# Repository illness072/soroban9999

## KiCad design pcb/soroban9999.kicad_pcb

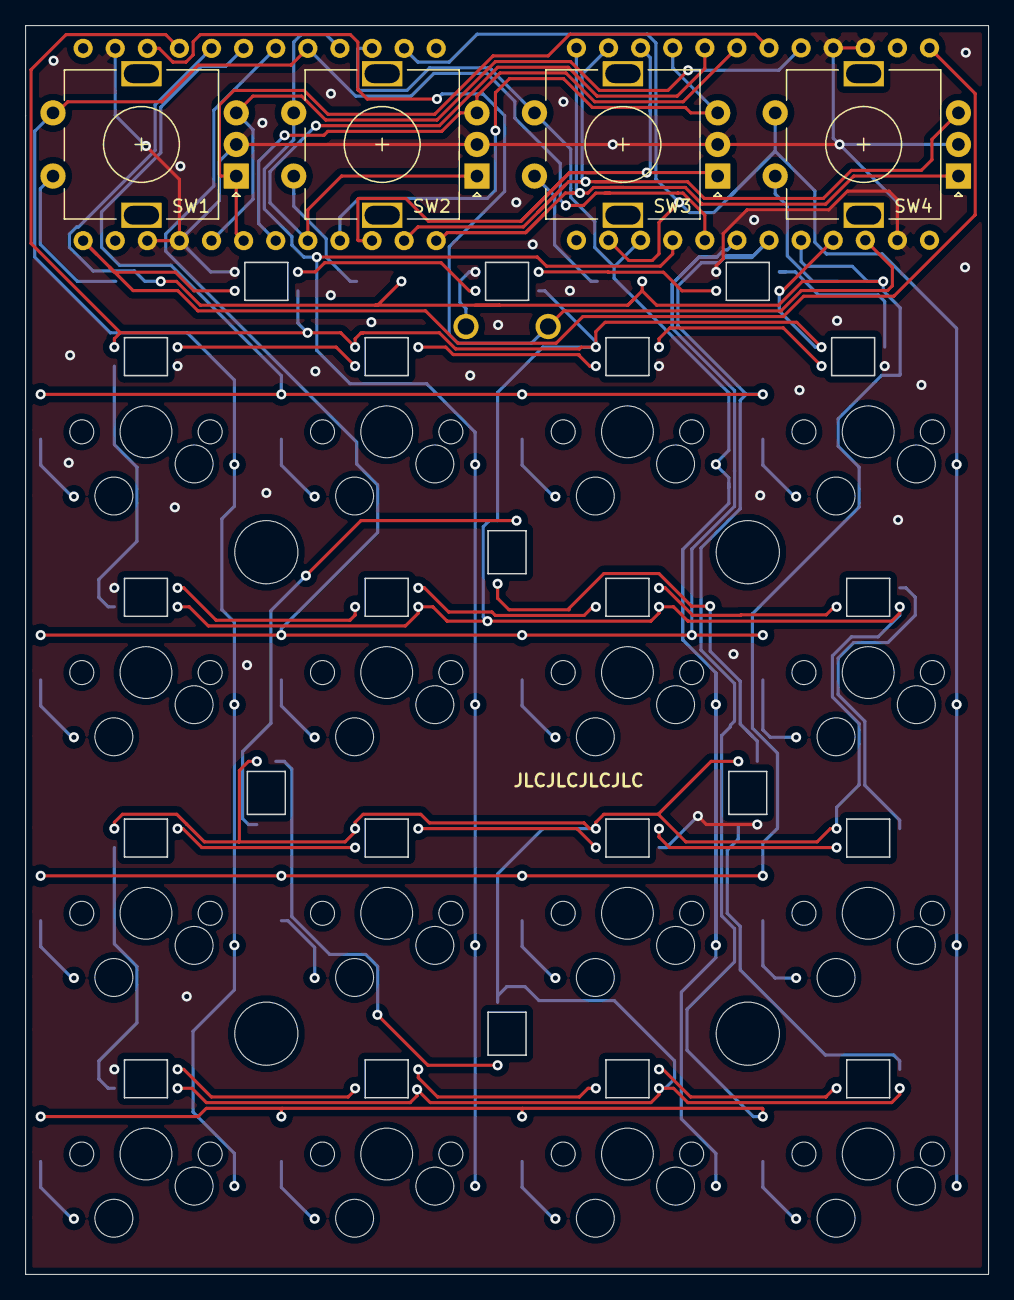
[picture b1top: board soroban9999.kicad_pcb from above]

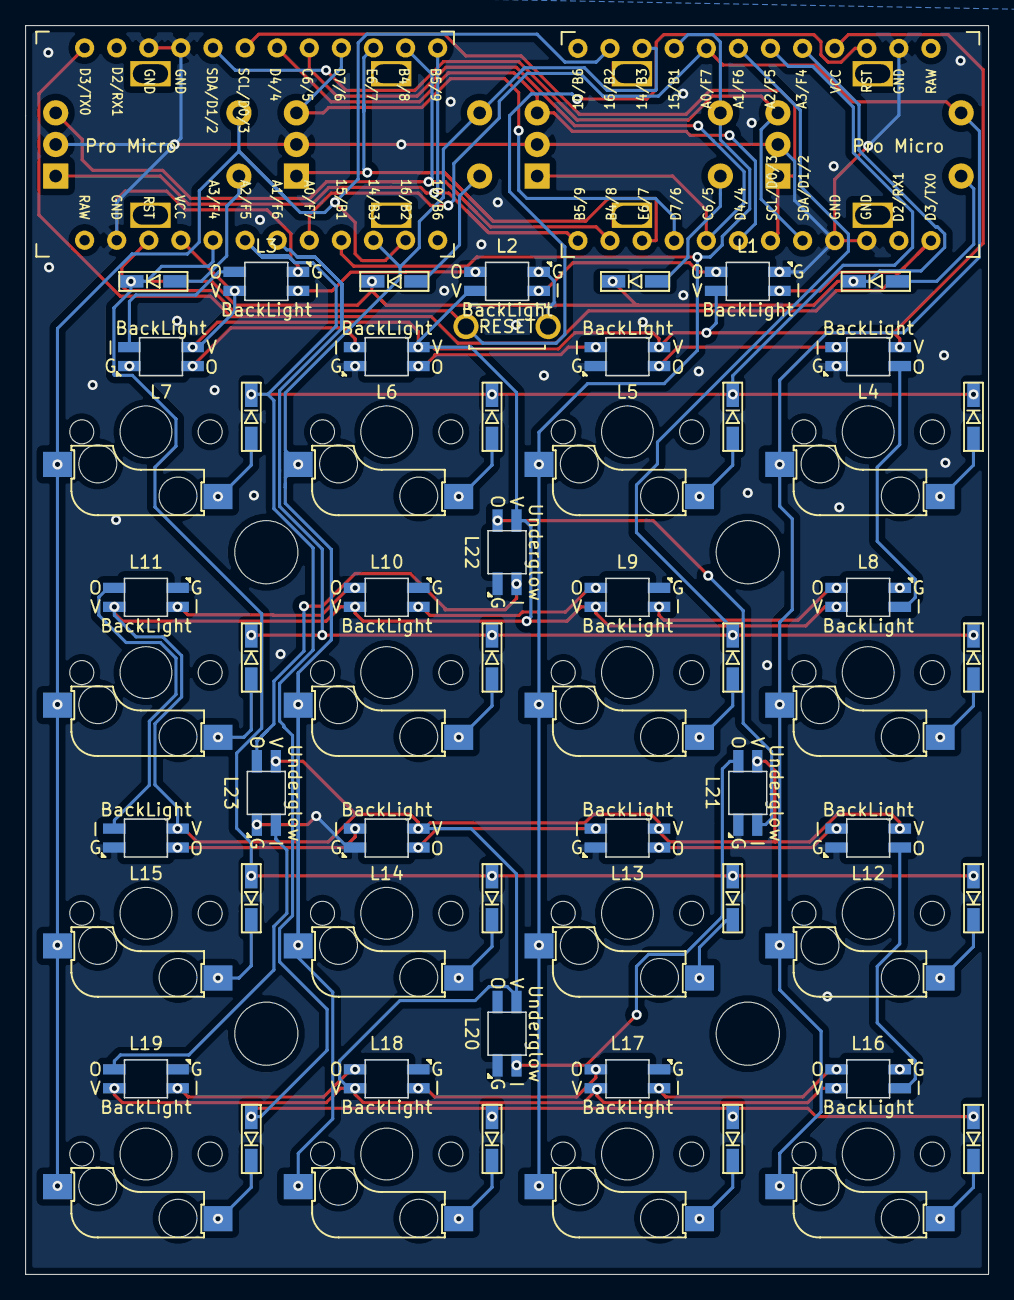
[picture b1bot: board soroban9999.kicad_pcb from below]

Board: 2 copper layers, 76.1 x 98.8 mm, 66 parts (46 on the bottom side), 61 nets.

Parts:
D1, D2, D3, D4, D5, D6, D7, D8, D9, D10, D11, D12, D13, D14, D15, D16, D17, D18, D19, D20: D; D3_SMD_v2
L1, L2, L3, L4, L5, L6, L7, L8, L9, L10, L11, L12, L13, L14, L15, L16, L17, L18, L19: YS-SK6812mini-E; YS-SK6812MINI-E
L20, L21, L22, L23: YS-SK6812mini-E; YS-SK6812MINI-E-underglow
R_SW1: SW_PUSH; ResetSW_1side
SW1, SW2, SW3, SW4: Rotary_Encoder_Switch; RotaryEncoder_Alps_EC11E-Switch_Vertical_H20mm
SW5, SW6, SW7, SW8, SW9, SW10, SW11, SW12, SW13, SW14, SW15, SW16, SW17, SW18, SW19, SW20: SW_PUSH; CherryMX_Hotswap
U1, U2: ProMicro; ProMicro_v3

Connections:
C0: SW1.S1, SW5.1, SW9.1, SW13.1, SW17.1, U1.17, U2.17
C1: SW2.S1, SW6.1, SW10.1, SW14.1, SW18.1, U1.16, U2.16
C2: SW3.S1, SW7.1, SW11.1, SW15.1, SW19.1, U1.15, U2.15
C3: SW4.S1, SW8.1, SW12.1, SW16.1, SW20.1, U1.14, U2.14
E0L: SW1.A, U1.6, U2.6
E0R: SW1.B, U1.5, U2.5
E1L: SW2.A, U1.8, U2.8
E1R: SW2.B, U1.7, U2.7
E2L: SW3.A, U1.10, U2.10
E2R: SW3.B, U1.9, U2.9
E3L: SW4.A, U1.12, U2.12
E3R: SW4.B, U1.11, U2.11
GND: L1.3, L2.3, L3.3, L4.3, L5.3, L6.3, L7.3, L8.3, L9.3, L10.3, L11.3, L12.3, L13.3, L14.3, L15.3, L16.3, L17.3, L18.3, L19.3, L20.3, L21.3, L22.3, L23.3, R_SW1.2, SW1.C, SW2.C, SW3.C, SW4.C, U1.3, U1.4, U1.23, U2.3, U2.4, U2.23
LED: L1.4, U1.1, U2.1
unnamed: D1.2, SW1.S2
unnamed: D2.2, SW2.S2
unnamed: D3.2, SW3.S2
unnamed: D4.2, SW4.S2
unnamed: D5.2, SW5.2
unnamed: D6.2, SW6.2
unnamed: D7.2, SW7.2
unnamed: D8.2, SW8.2
unnamed: D9.2, SW9.2
unnamed: D10.2, SW10.2
unnamed: D11.2, SW11.2
unnamed: D12.2, SW12.2
unnamed: D13.1, SW13.2
unnamed: D14.1, SW14.2
unnamed: D15.1, SW15.2
unnamed: D16.1, SW16.2
unnamed: D17.1, SW17.2
unnamed: D18.1, SW18.2
unnamed: D19.1, SW19.2
unnamed: D20.1, SW20.2
unnamed: L1.2, L2.4
unnamed: L2.2, L3.4
unnamed: L3.2, L7.4
unnamed: L4.2, L8.4
unnamed: L4.4, L5.2
unnamed: L5.4, L6.2
unnamed: L6.4, L7.2
unnamed: L8.2, L9.4
unnamed: L10.2, L11.4
unnamed: L9.2, L10.4
unnamed: L11.2, L15.4
unnamed: L12.2, L16.4
unnamed: L12.4, L13.2
unnamed: L13.4, L14.2
unnamed: L14.4, L15.2
unnamed: L16.2, L17.4
unnamed: L17.2, L18.4
unnamed: L18.2, L19.4
unnamed: L19.2, L23.4
unnamed: L20.4, L21.2
unnamed: L21.4, L22.2
unnamed: L22.4, L23.2
R0: D1.1, D2.1, D3.1, D4.1, D13.2, D14.2, D15.2, D16.2, U1.20, U2.20
R1: D5.1, D6.1, D7.1, D8.1, D17.2, D18.2, D19.2, D20.2, U1.19, U2.19
R2: D9.1, D10.1, D11.1, D12.1, U1.18, U2.18
RST: R_SW1.1, U1.22, U2.22
VCC: L1.1, L2.1, L3.1, L4.1, L5.1, L6.1, L7.1, L8.1, L9.1, L10.1, L11.1, L12.1, L13.1, L14.1, L15.1, L16.1, L17.1, L18.1, L19.1, L20.1, L21.1, L22.1, L23.1, U1.21, U2.21

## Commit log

2021-05-04 add some datas
2022-05-14 Add plate data for Yusha-Kobo laser cut
2022-05-15 Fix plate data
2022-05-16 Add plate data for Yusha-Kobo laser cut (#1)
    * Add plate data for Yusha-Kobo laser cut
    * Fix plate data
